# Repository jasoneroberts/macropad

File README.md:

# Macropad with a screen

A wireless macropad with MX keys, an EC11 knob and a small LCD that shows what each key does. It is built on the same nRF52840 / Zephyr / nRF Connect SDK stack as the [trackball](https://github.com/jasoneroberts/NordicMouseProject), with a 3D-printed case and a hand-soldered PCB. Started 2026-10-20.

Status 2026-10-21: concept B (12 keys, 2.0″ screen) and the SuperMini nRF52840 controller are chosen. The case model, firmware and PCB inputs exist for all three concepts; the firmware compiles but has not run on hardware yet, and nothing has been printed. Next: buy the screen and an EC11 knob and try the firmware on the nRF52840 DK.

Status 2026-11-11: the concept B main PCB is designed in full (schematic, placement, routing, ground pours) with its parts in a shared JR component library, ready to import into Altium 19 and order from JLCPCB: see `pcb/B/altium/README.md`. The controller pin map changed with it (LCD on footprint pins 5-10, rows 0/1 on P1.15/P0.02); the firmware and case follow.

| | A · Pocket | B · Studio (chosen) | C · Deck |
|---|---|---|---|
| Keys | 3 × 3 MX hot-swap | 4 × 3 MX hot-swap | 4 × 4 MX hot-swap |
| Knob (EC11) | Ø26 | Ø28 | Ø36 |
| Screen | 1.69″ ST7789V2 240 × 280, portrait | 2.0″ ST7789 320 × 240, landscape | 1.28″ GC9A01 240 × 240, round |
| Footprint on desk | 76 × 122 mm | 101 × 118 mm | 92 × 142 mm |
| Height front / rear | 12.5 / 25.1 mm | 12.5 / 24.6 mm | 12.5 / 29.5 mm |
| Tilt | 6° | 6° | 7° |
| LiPo | 603040 | 603040 | 803040 |

Heights are without the 10 mm rubber feet (add about 2 mm).

## Folder

| Path | What |
|---|---|
| `scad/macropad.scad` | The parametric model. Every dimension is a named parameter at the top. |
| `stl/<A,B,C>/print/` | `top`, `bottom`, `knob`, `clamp`, already oriented for the printer bed. |
| `stl/<A,B,C>/view/` | Every part and dummy component (PCB, switches, display, controller, battery) in the assembled position. Made by `tools/build.py`; not kept in git. |
| `stl/test_coupon.stl` | Print this first: switch holes 13.9 / 14.0 / 14.1 / 14.2 (1 to 4 dots) and two insert holes. |
| `dxf/pcb_outline_<c>.dxf` | Main PCB outline with MX centre holes (Ø4) and pillar holes (Ø2.2), for Altium. Plate-frame mm, origin at the case's front-left corner. |
| `build/report_<c>.json` | Dimensions and positions of everything, plus the fit-check result. |
| `build/viewer_<c>.glb` | Coloured assembly. Opens in Windows 3D Viewer. |
| `build/fitcheck.txt` | Overlap check between all parts. Should say `OK` for each concept. |
| `page/index.html` | The concept comparison page with 3D viewers. Made by `tools/make_page.py`; not kept in git. |
| `tools/` | `build.py` (STLs, DXF, report, fit check, GLB), `drawings.py` (plan and section SVGs), `make_page.py` + `page_template.html`, `build_firmware.sh` (Linux: installs NCS v3.3.0 and builds all six firmware variants; CI runs it too). |
| `firmware/` | Zephyr / NCS v3.3.0 app: keys, knob, LVGL screen, USB + Bluetooth HID. See `firmware/README.md`. |
| `firmware/prebuilt/` | Ready-to-flash concept B images: `macropad_B_promicro.uf2` and `macropad_B_dk.hex`. GitHub Actions also builds them on every firmware change (the run's "Artifacts"). |
| `pcb/` | The concept B board for Altium (`pcb/B/altium/`), its KiCad working copy and scripts (`pcb/B/kicad/`, `pcb/board/`), the shared JR component library (`pcb/library/`), and `generate.py`'s starting kits for all three concepts. See `pcb/README.md`. |
| `SHOPPING.md` | What to buy for B (UK prices) and what to measure when it arrives. |
| `LICENSES/` | Upstream licences for the files based on Nordic and Zephyr samples (see "Licences" below). |

## Rebuild after changing a parameter

Needs OpenSCAD 2021.01 or newer, Python 3 and `pip install trimesh manifold3d numpy scipy networkx`.

From the repo root:

```
python tools/build.py          # all concepts (or: build.py B)
python tools/drawings.py
python pcb/generate.py         # needs pip install shapely
python tools/make_page.py page
```

To export one part by hand: `openscad -D 'concept="B"' -D 'part="top_print"' -o top.stl scad/macropad.scad`. Open the file in the OpenSCAD GUI to use the Customizer for `concept` and `part`.

## Measure before printing

These come from listings or datasheets, not from parts on the bench:

- Display glass outline, thickness and where the active area sits on the glass (`LCD169`, `LCD200`, `GC9A01` tables). Board sizes and active areas are from Waveshare; glass outlines are estimates.
- EC11 body height above the PCB (`enc_body_h`, 6.5) and shaft length (`enc_shaft_l`, 15).
- Heat-set insert hole (`insert_d` 4.0, `insert_len` 4.0 for M3 × 4 short inserts).
- LiPo size (`LIPO_603040`, `LIPO_803040`).
- Switch hole (`sw_hole` 14.0): use the test coupon.

## How it's built

- Top shell = switch plate. 3 mm skin: 1.5 mm lip with the 14 mm hole, 15 mm pocket below for the MX clips. PCB top 5.0 mm below the plate top (MX standard), Kailh sockets under the PCB.
- The top surface is tilted, the bottom plate is flat, so the inside gets deeper toward the back. LiPo, controller and display stack live under the rear band.
- Display: window = active area + 0.4 mm with a 45° chamfer through a 1 mm bezel; glass in a pocket; printed clamp with two M2 screws holds the module board. Main PCB has a cut-out there; 8 wires to the module.
- Controller: SuperMini nRF52840 (chosen 2026-10-21; a nice!nano v2 also fits) on 2.5 mm headers under the PCB, component side down, USB-C (mid-mount, centred on the 1.6 mm module board) through a 13 × 7.5 mm rear opening.
- Four M3 countersunk screws into M3 heat-set inserts in the corner bosses; M2 self-tapping screws for the PCB pillars and the display clamp; slide switch slot in the right wall for the OS102011MA1QN1's actuator.
- Prints without supports: top shell face down, bottom plate and clamp flat, knob top face down. Largest part is C's top shell, 92 × 140 mm.

## Licences

No licence has been chosen for the project as a whole yet, so the default applies (all rights reserved). Two kinds of file keep their upstream licence, named by the `SPDX-License-Identifier` line at the top of the file:

- `firmware/src/BT.c` is based on Nordic's `peripheral_hids_keyboard` sample: `LicenseRef-Nordic-5-Clause` (`LICENSES/LicenseRef-Nordic-5-Clause.txt`), which allows use only with Nordic chips.
- `firmware/CMakeLists.txt` and `firmware/Kconfig` come from Zephyr's USB samples: Apache-2.0 (`LICENSES/Apache-2.0.txt`).

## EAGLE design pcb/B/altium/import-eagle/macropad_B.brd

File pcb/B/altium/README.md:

# Macropad concept B main board: Altium package

This folder takes the concept B main board into Altium Designer 19 as a **finished design**: schematic drawn, every part placed, every track routed, ground poured on both sides. You import it once with Altium's Import Wizard, check it, set the rules, repour, run the design rule check and make the Gerbers for JLCPCB.

Rough time: 30 minutes for the library and the import, 20 minutes for checks and rules, 10 minutes for Gerbers.

| | |
|---|---|
| Board | 95.3 x 110.45 mm, 2 layers, 1.6 mm, hand-soldered (0805, SOD-123, through-hole and the SuperMini on headers) |
| Parts | 40: U1 SuperMini nRF52840, 12 hot-swap sockets, 13 diodes, ENC1 encoder, power switch, reset switch, JST battery header, LCD wire pads, 3 capacitors, 2 test pads, 4 mounting holes |
| Nets | 35 |
| Copper | 253 track segments, 9 vias, a GND pour on each side. Every connection, ground included, is a track; the pours add shielding on top. KiCad's checks: 0 unrouted connections, 0 copper rule errors |
| Coordinates | mm in the case's plate frame: origin at the case's front-left corner, x to the right, y toward the screen end. The board's own bottom-left corner is at (2.85, 2.85) |

## What's in this folder

| Folder / file | What it is |
|---|---|
| `import-eagle/macropad_B.sch`, `macropad_B.brd` | **The design**, as EAGLE files for Altium 19's Import Wizard (Step 2). |
| `library/JR.lbr` | The whole JR component library (22 parts, the macropad's and the trackball carrier's) for Step 1. The same file is in `pcb/library/` in the repo. |
| `library/JR_parts.csv` | The library's part list: symbol, footprint, value, description, manufacturer, part number, LCSC number. |
| `library/JR_preview.pdf` | One page per library part: symbol, footprint and parameters. |
| `reference/macropad_B-schematic.pdf` | The schematic (A3), to read alongside the imported one. |
| `reference/macropad_B-board.pdf` | The board from the top: red = top copper, blue = bottom copper, shaded = pours. |
| `reference/placement.csv` | Every part's side, X, Y, rotation and pin 1 position. |
| `reference/connections.csv` | Every pin and the net it's on. |
| `reference/BOM.csv`, `reference/order-list.csv` | Parts list, and what to buy where, with LCSC numbers. |
| `reference/gerbers-reference/` | Gerbers and drill files made by KiCad from the same board. Compare Altium's against these (Step 6). |

## How this design was made, and why it reaches Altium as EAGLE files

The design lives in the repo as Python (`pcb/board/`): `design_b.py` holds the parts, the nets, the pin map and where each part must sit for the case; `build_board.py` places the parts and draws the outline from the case model; `route.py` routes it with Freerouting and pours the ground; `schematic.py` draws the schematic. KiCad 7 is the engine underneath: it holds the board while it's built and runs the design rule check.

Altium 19 has no KiCad importer (it arrived in Altium 20.1), but it does import EAGLE. EAGLE files are plain XML, so `export_altium.py` writes the board and the schematic in EAGLE's format, and two checks run on them before they reach you:

- `check_eagle.py` reads the two files the way Altium will: every schematic pin sits on the end of a wire of its own net, nothing touches a pin of another net, and the nets built from the schematic are exactly the board's nets (35 nets, 104 pins; the only unconnected pins are U1's spare P0.08 and the power switch's unused third pin).
- KiCad's own EAGLE importer reads the board back: all 172 pads, 253 tracks and 9 vias land within 0.003 mm of the original, on the right nets.

EAGLE has a few rules that shape what you'll see after the import. None of them change the circuit:

- **Surface-mount pads have to be on the top of an EAGLE footprint.** Parts that sit on the bottom of this board are stored the normal way and placed *mirrored* (EAGLE rotation `MR...`). Altium turns that into a part on the Bottom Layer. The hot-swap socket footprint is drawn from the socket's side for the same reason; see "Library notes" below.
- **Pin names must be unique.** The SuperMini's three GND pins arrive as `GND`, `GND@4` and `GND@23`. Pin numbers (Altium's pin *designators*) are unaffected.
- **Through-hole pads can only be round or square.** Oval pads arrive round at their narrow width: the slide switch's pins (1.5 mm) and mounting legs (2.2 mm), and the battery header's pins (1.2 mm). They're still big enough to solder; Step 4.7 says how to make them oval again.
- **There are no slots.** The encoder's two mounting-lug slots arrive as round 1.5 mm holes, with the slot's outline drawn on a mechanical layer. Step 4.6 turns them back into 2.8 x 1.5 mm slots. This one matters: the lugs won't fit a round hole.

## Before you start

1. **Unzip or copy the package** to a short path, for example `C:\Users\jason\OneDrive\Documents\Projects\WirelessTrackballProject\PCB\macropad-altium\`.
2. **Close the Gameball carrier project** in Altium if it's open, so nothing from it gets mixed in.
3. **Units:** press `Q` in any PCB view until the status bar shows mm.

## Step 1: Install the JR library (once, for every design)

The JR library is your own component library: one symbol per kind of part (a resistor, a diode, the SuperMini), one footprint per package, and one *component* per orderable part that ties a symbol to a footprint and carries the part data (value, description, manufacturer, part number, LCSC number). The macropad and the carrier both use it, and new designs can too. It lives in `D:\Jase\Nas\Engineering\PCB Design\Altium\Libraries\`.

In Altium terms you end up with:

- `JR.SchLib` (schematic symbols) and `JR.PcbLib` (footprints): the source files you edit.
- `JR.LibPkg`: an *integrated library package*, a small project that lists those two files.
- `JR.IntLib`: the compiled, read-only library that designs place parts from. You recompile it after every edit.

The same files, with the Gameball relink table and a parts preview, are in `D:\Jase\Nas\Engineering\PCB Design\Altium\Libraries\`; use that copy for every board. Once `JR.IntLib` exists, install it for all projects: Components panel menu » **File-based Libraries Preferences » Installed » Install**.

Steps:

1. **File » Import Wizard » Next**, pick **EAGLE Projects and Designs**, **Next**.
2. **Design files:** add nothing. **Next.**
3. **Library files:** **Add** `library\JR.lbr`. **Next.**
4. **Settings page:** tick **Log All Errors / Warnings / Events**. Set the **output directory** to `D:\Jase\Nas\Engineering\PCB Design\Altium\Libraries\`. **Next**, then **Finish**.
5. You now have `JR.SchLib` and `JR.PcbLib` in that folder (open them from **File » Open** if the wizard didn't). Open the SchLib, pick a few components in the **SCH Library** panel, and check:
   - the **Parameters** list has `MANUFACTURER`, `MPN`, `LCSC` and `DESCRIPTION` (and the **Comment** shows the value, for example `1N4148W`);
   - the **Models** list has a footprint with the same name as in `JR_parts.csv`, and its preview shows the footprint.
6. **Make the package:** **File » New » Project**, type **Integrated Library**, name `JR`, location `D:\Jase\Nas\Engineering\PCB Design\Altium\Libraries\`. Right-click `JR.LibPkg` in the **Projects** panel » **Add Existing to Project** » pick `JR.SchLib` and `JR.PcbLib`. **File » Save All.**
7. **Compile it:** right-click `JR.LibPkg` » **Compile Integrated Library JR.LibPkg**. The Messages panel should show no errors. Altium writes `Project Outputs for JR\JR.IntLib` and adds it to the **Components** panel. If the panel doesn't list it: **Components panel » ☰ » File-based Libraries Preferences » Installed » Install** and pick the `.IntLib`.
8. **Optional tidy-up**, which you can do any time (recompile afterwards):
   - Rename the parameters to Altium's usual names with **Tools » Parameter Manager** in the SchLib: `MANUFACTURER` → `Manufacturer`, `MPN` → `Manufacturer Part Number`, `DESCRIPTION` → the component's **Description** field.
   - Give the SuperMini's GND pins plain names (`GND@4` → `GND`).

*Why an IntLib and not just the two files?* The compiled library carries the symbol, footprint and parameters together, and Altium checks on compile that every symbol pin has a pad to go to. Designs then link to `JR.IntLib`, so a change you make once (a footprint fix, a new LCSC number) reaches every design with **Tools » Update From Libraries**.

## Step 2: Import the design

1. **File » Import Wizard » Next**, pick **EAGLE Projects and Designs**, **Next**.
2. **Design files:** **Add** `import-eagle\macropad_B.sch` and `import-eagle\macropad_B.brd` (Ctrl-click both, or one after the other). **Next.**
3. **Library files:** add nothing (the design files carry their own copy of the parts). **Next.**
4. **Layer mapping** (if your version shows the grid; otherwise Altium uses its defaults and you check the result in Step 3):

   | EAGLE layer | Altium layer | What's on it |
   |---|---|---|
   | 1 Top / 16 Bottom | Top Layer / Bottom Layer | Tracks, pads, the two GND pours |
   | 20 Dimension | Mechanical 1 | **Board outline** |
   | 21 tPlace / 22 bPlace | Top Overlay / Bottom Overlay | Silkscreen |
   | 25 tNames / 26 bNames | Top Overlay / Bottom Overlay | Designators |
   | 27 tValues / 28 bValues | Top Overlay / Bottom Overlay | Values (hidden) |
   | 41 tRestrict / 42 bRestrict | Keep-Out (top / bottom copper) | No copper round the four M2 screw holes |
   | 46 Milling | a spare mechanical layer, for example Mechanical 4 | Outline of the encoder's two lug slots |
   | 51 tDocu / 52 bDocu | Mechanical 13 / Mechanical 14 | Part bodies (assembly drawing) |

5. **Settings page:**
   - **General:** tick **Log All Errors / Warnings / Events**.
   - **Schematic:** **untick Recognize powerports and Recognize ports.** This design connects everything by wires and net labels; with these ticked, Altium can turn parts whose names match its patterns into port symbols.
   - **PCB:** leave **Generate 3D body** unticked.
   - **Output directory:** a new empty folder, for example `...\macropad-altium\altium-project\`.
6. **Next**, wait, **Finish**. Read the log: font and unused-layer warnings are fine; tell me about anything else.
7. **One project:** if the Projects panel shows two projects (one with the `.SchDoc`, one with the `.PcbDoc`), right-click the one with the `.SchDoc` » **Add Existing to Project** » pick the `.PcbDoc`, then close the other project. **File » Save All.**
8. **Link schematic and PCB parts:** EAGLE files don't carry Altium's hidden Unique IDs, so link them once by designator. Open the `.PcbDoc`, **Project » Component Links**, **Add Pairs Matched By** with *Designator* ticked, check all 40 parts are in the matched list, **Perform Update**. **File » Save All.**

## Step 3: Check the import (10 minutes)

1. **Compile:** **Project » Compile PCB Project**. Open **Messages**. No errors expected. EAGLE has no no-connect markers, so U1 pin 2 (P0.08) and SW_PWR pin 3 may be listed as unconnected: that's correct. Put **Place » Directives » Generic No ERC** on them for a clean list.
2. **Schematic and PCB agree:** in the `.PcbDoc`, **Design » Update PCB Document**. After Step 2.8 the list should be empty, or only offer *Rooms* and *Component Classes* (untick those). If it wants to change nets or replace parts, click **Cancel** and tell me what it lists.
3. **Board shape:** press `2`. The board is the L shape: full width at the front (keys), only the right-hand strip at the back (controller and knob), with the big opening for the screen at the back left and a dip round the screen clamp's pillar. Three corner notches (front left, front right, back right) clear the case's screw bosses; the fourth boss sits in the screen opening, off the board. If the board area is a plain rectangle: click the outline on Mechanical 1, press `Tab` to select all of it, **Design » Board Shape » Define from selected objects**.
4. **Origin:** the EAGLE coordinates are the case's plate frame, so Altium's origin should already be the case's front-left corner, 2.85 mm below and left of the board's corner. If the numbers below don't match, **Edit » Origin » Set** and type or click (0, 0) accordingly.
5. **Spot-check five parts.** Click the part, read X, Y and Layer in **Properties**; then click its pin 1 pad and check the pad's position. Pin 1 is the unambiguous check for bottom-side parts, because Altium and EAGLE count rotation differently for mirrored parts.

   | Part | Layer | X | Y | Pin 1 at |
   |---|---|---|---|---|
   | U1 | Bottom | 82.000 | 96.250 | (89.620, 110.220), square pad, back right |
   | ENC1 | Top | 82.000 | 87.650 | pin A (79.500, 80.150), square pad |
   | SW1 | Bottom | 21.925 | 55.625 | pad 1 (14.840, 58.165) |
   | J2 | Bottom | 93.600 | 105.140 | pin 1 (93.600, 105.140), square pad, back end |
   | SW_RST | Bottom | 74.500 | 66.125 | pad 1 (71.500, 64.250) |

   `reference/placement.csv` has the rest.
6. **Nets:** **PCB panel » Nets**: 35 nets. 3V3_SW, COL0-COL4, DBG_TX, ENC_A, ENC_B, GND, K1-K12, K_PUSH, LCD_BL, LCD_CS, LCD_DC, LCD_MOSI, LCD_RST, LCD_SCK, NRST, ROW0-ROW2, VBAT, VBAT_SW. `reference/connections.csv` lists every pin.
7. **Tracks:** compare with `reference/macropad_B-board.pdf`. Nearly all routing is on the bottom, so the top stays one solid ground plane under the keys.

## Step 4: Rules, pours and the two fix-ups

Open **Design » Rules**. These are the values the board was routed and checked with in KiCad, with margin over JLCPCB's standard limits.

1. **Net class:** **Design » Classes » Net Classes** should have `power` with GND, VBAT, VBAT_SW and 3V3_SW. Add it if the import didn't.
2. **Electrical » Clearance:** 0.2 mm. Add a second Clearance rule, scope *InPolygon* to *All*, 0.3 mm, priority above the first: the pours keep 0.3 mm from everything else, as they did in KiCad.
3. **Routing » Width:** default min 0.2, preferred 0.25, max 1.0 mm. Second rule, scope *InNetClass('power')*: min 0.3, preferred 0.4, max 1.0 mm, priority above the default.
4. **Routing » Routing Via Style:** diameter 0.6 mm, hole 0.3 mm.
5. **Manufacturing:** **Hole Size** min 0.3, max 4.1 mm (the MX switch centre holes are 4.0 mm). **Board Outline Clearance** 0.3 mm. **Hole To Hole Clearance** 0.25 mm. **Minimum Annular Ring** 0.15 mm.
6. **Encoder lug slots.** Do this in the library so every design gets it: open `JR.PcbLib`, footprint `RotaryEncoder_EC11_Switch_NPTH`. Double-click each of the two unnamed holes at (0, ±5.6): **Hole Type: Slot**, **Hole Size 1.5 mm**, **Length 2.8 mm**, **Rotation 0**, **Plated: off**. Pad size equal to the hole, no copper. Save, recompile `JR.LibPkg`. In the design, in the `.PcbDoc`: **Tools » Update From PCB Libraries**, pick ENC1 only. On the board the slots then run front to back at x = 76.4 and 87.6, between U1's two pin rows, 0.42 mm from U1's pads. Delete the slot outlines on the milling layer afterwards (they were only there to show where the slots go).
7. **Oval pads (optional):** in the PcbLib, `SW_Slide_SPDT_Angled_CK_OS102011MA1Q` pins 1-3 back to 1.5 x 2.5 mm *Round* (Altium draws that as an oval) and MP1/MP2 to 2.2 x 3.5 mm; `JST_PH_S2B-PH-K_1x02_P2.00mm_Horizontal` pins to 1.2 x 1.75 mm. Update the design from the library as in item 6.
8. **Pours:** the two GND polygons (top and bottom) came in with the design, already shaped: inset 0.3 mm from the edge, and with a gap over the whole SuperMini so no copper sits near its antenna. Check each one's net is `GND`, **Pour Over All Same Net Objects**, **Remove Dead Copper** ticked. Then **Tools » Polygon Pours » Repour All**.
9. **Pour connections:** **Plane » Polygon Connect Style:** *Relief Connect*, 4 entries, conductor width 0.4 mm, air gap 0.3 mm. That's what KiCad used. Repour again if you changed it.
10. **Screw-hole keep-outs:** the four M2 holes (H1-H4) each have a round keep-out on both copper layers, 2.6 mm radius, so the screw heads underneath can't touch copper. Check they came through (they show on the Keep-Out layer). If not, draw a 5.2 mm keep-out circle round each hole on Top and Bottom.

## Step 5: Design rule check

**Tools » Design Rule Check » Run Design Rule Check.** Expected:

- **0 Un-Routed Net Constraint** violations. All 12 ground pads have ground tracks, so this holds even before the pours are filled; if Altium reports a pour as unconnected *dead copper*, the Remove Dead Copper option in Step 4.8 takes it out.
- **0 clearance, width, short-circuit or hole-size violations.**
- **Silkscreen warnings are fine:** some stock footprints draw silk across their pads (the hot-swap socket and the slide switch, for example), and the SuperMini's outline runs off the board at the back-right notch. JLCPCB clips silk off pads and the board edge. Fix them if you like the board tidy.

## Step 6: Gerbers and drill files for JLCPCB

1. **Gerbers:** **File » Fabrication Outputs » Gerber Files**. Units *Millimeters*, format *4:4* (or *Inches 2:4*, both fine for JLC). **Layers** tab: **Plot Layers » Used On**; among the mechanical layers tick **only Mechanical 1** (the outline). **OK**.
2. **Drill:** **File » Fabrication Outputs » NC Drill Files**, same units and format. Tick **Generate separate NC Drill files for plated & non-plated holes**. **OK**, and **OK** on the drill-size pop-up.
3. **Compare with the reference:** open both sets in a Gerber viewer (JLCPCB's upload preview, or Altium's **File » Open** on the `.GTL` etc., which opens CAMtastic). Things to see in Altium's set: the L-shaped outline with three boss notches and the shallow dip in the back edge; the encoder's two **slots** (not round holes) in the non-plated drill file; 9 vias; no copper under the SuperMini; the GND pour on both sides.
4. **Zip** the Gerber and drill files from `Project Outputs for ...`.
5. **Order at JLCPCB:** 2 layers, 1.6 mm, 5 boards, any colour, HASL with lead (easiest to hand-solder). The board is over 100 mm in one direction, so it costs a few pounds more than the 100 x 100 mm price.

`reference/gerbers-reference/` is a complete set from KiCad (plate-frame coordinates, slots in the NPTH drill file). If Altium's output ever disagrees with it, ask me before ordering.

## Step 7: Check before ordering boards

A mistake in any of these means a new board. Print the board 1:1 first (**File » Page Setup**, *Scaled Print*, scale 1.00; check the board measures 95.3 mm across) and lay real parts on the paper.

1. **SuperMini at the back right, under the board.** U1 hangs under the board on its headers with its components facing down toward the desk (its plain back toward the PCB), USB-C toward the back wall. Turn the print over and lay a SuperMini on the bottom view, components up: its pin labels must match the schematic (pin 1 = P0.06 at the back right seen from the top, B+ at the back left), and USB must point at the back edge. The pin positions are the standard Pro Micro ones (rows 15.24 mm apart, 2.54 mm pitch).
2. **Encoder.** Fit a real PEC11R-4220F-S0024 through the print: 5 pins (A, C, B on one side; S1, S2 on the other) and the two lugs on the slots. The lugs and pins are trimmed flush on the bottom before U1 goes on, because U1 sits right under them.
3. **Power switch reach.** The OS102011MA1QN1's actuator should stick 0.9 mm out of the right-hand wall at y = 72. The case slot has been adjusted to the switch's 2 x 4 mm actuator; print the case's right wall section if you want to try it before the PCB arrives.
4. **Battery polarity.** J1 pin 1 (square pad, the one nearer the front) is `VBAT` (+), pin 2 is GND; the plug goes in from the left. LiPo leads come both ways round: check yours before plugging in, and swap the pins in the plug if it's reversed.
5. **LCD cable order.** J2 pins 1-8 are VCC, GND, DIN, CLK, CS, DC, RST, BL from the back, which is the Waveshare cable order. Check the colours on your cable against the module's labels when it arrives.
6. **Heights.** U1 on 2.5 mm low-profile headers; nothing on the top side may poke up more than 2 mm (the gap under the case skin), so trim every through-hole joint flush on the top.

## Assembly order

1. Diodes D1-D13 and capacitors C1-C3 (bottom).
2. Hot-swap sockets SW1-SW12 (bottom).
3. SW_RST, SW_PWR, J1 (bottom).
4. ENC1 from the top; **trim its five pins and two lugs flush underneath**, and put Kapton tape over the area.
5. U1 on its low-profile headers (bottom). Trim the pins flush on the top.
6. LCD cable into J2 from the bottom, solder on the top, trim flush.

## Library notes

- **The hot-swap socket footprint is drawn from the socket's side.** EAGLE (and so the import) only allows surface-mount pads on top, so `SW_Kailh_MX_Hotswap` has its pads on the top layer and is mirrored left-to-right. Placed on the **bottom** layer it comes out right: the holes line up with the switch above, the pads land on the bottom copper where the socket is soldered. Always place it on the bottom. If you'd rather have it the Altium way (drawn from the top, pads on the bottom layer), redraw it in the PcbLib.
- The JR library also holds the carrier's parts (XIAO nRF52840, SS14, DMG2305UX, 0805 resistors and capacitors, the connectors). The carrier project stays linked to its own imported library until you decide to switch it over.
- To add a part later: draw the symbol in `JR.SchLib` (or reuse one: every resistor uses `R`), the footprint in `JR.PcbLib`, set the parameters (`Manufacturer`, `Manufacturer Part Number`, `LCSC`, `Description`), recompile. `JR_parts.csv` shows the pattern.

## What changed elsewhere with this board

- **Controller pin map:** footprint pins 5-10 now carry the LCD's six signals in the Waveshare cable order (P0.17 MOSI, P0.20 SCK, P0.22 CS, P0.24 DC, P1.00 RST, P0.11 backlight), so they run straight across to J2. Rows 0 and 1 moved to P1.15 and P0.02. The firmware's board overlay, `pcb/generate.py` and `pcb/README.md` are updated to match, and the firmware rebuilt.
- **Case:** knob moved 1 mm left to x = 82 (centred over the SuperMini, so the encoder's lug slots fall between its pin rows); the PCB outline opens the screen cut-out to the back and left edges and clears the screen clamp pillar by 0.5 mm; boss notches 8.8 mm across; the case trims 0.4 mm round the PCB edge at board height; USB-C opening raised for the SuperMini's mid-mount connector; power switch modelled as the OS102011MA1QN1.

## Rebuilding this package

Everything here is generated. After changing the design, from the repo root on a machine with KiCad 7 and Freerouting:

```
/usr/bin/python3 pcb/library/src/build_library.py            # JR library
/usr/bin/python3 pcb/board/build_board.py pcb/B/kicad        # place parts, outline, pours
/usr/bin/python3 pcb/board/route.py pcb/B/kicad freerouting-1.9.0.jar
/usr/bin/python3 pcb/board/check.py pcb/B/kicad/macropad_B.kicad_pcb
/usr/bin/python3 pcb/board/export_altium.py pcb/B/kicad pcb/B/altium
python3 pcb/board/check_eagle.py pcb/B/altium/import-eagle
```

Once you've imported into Altium and started editing there, the Altium project is the master copy and these files are history.

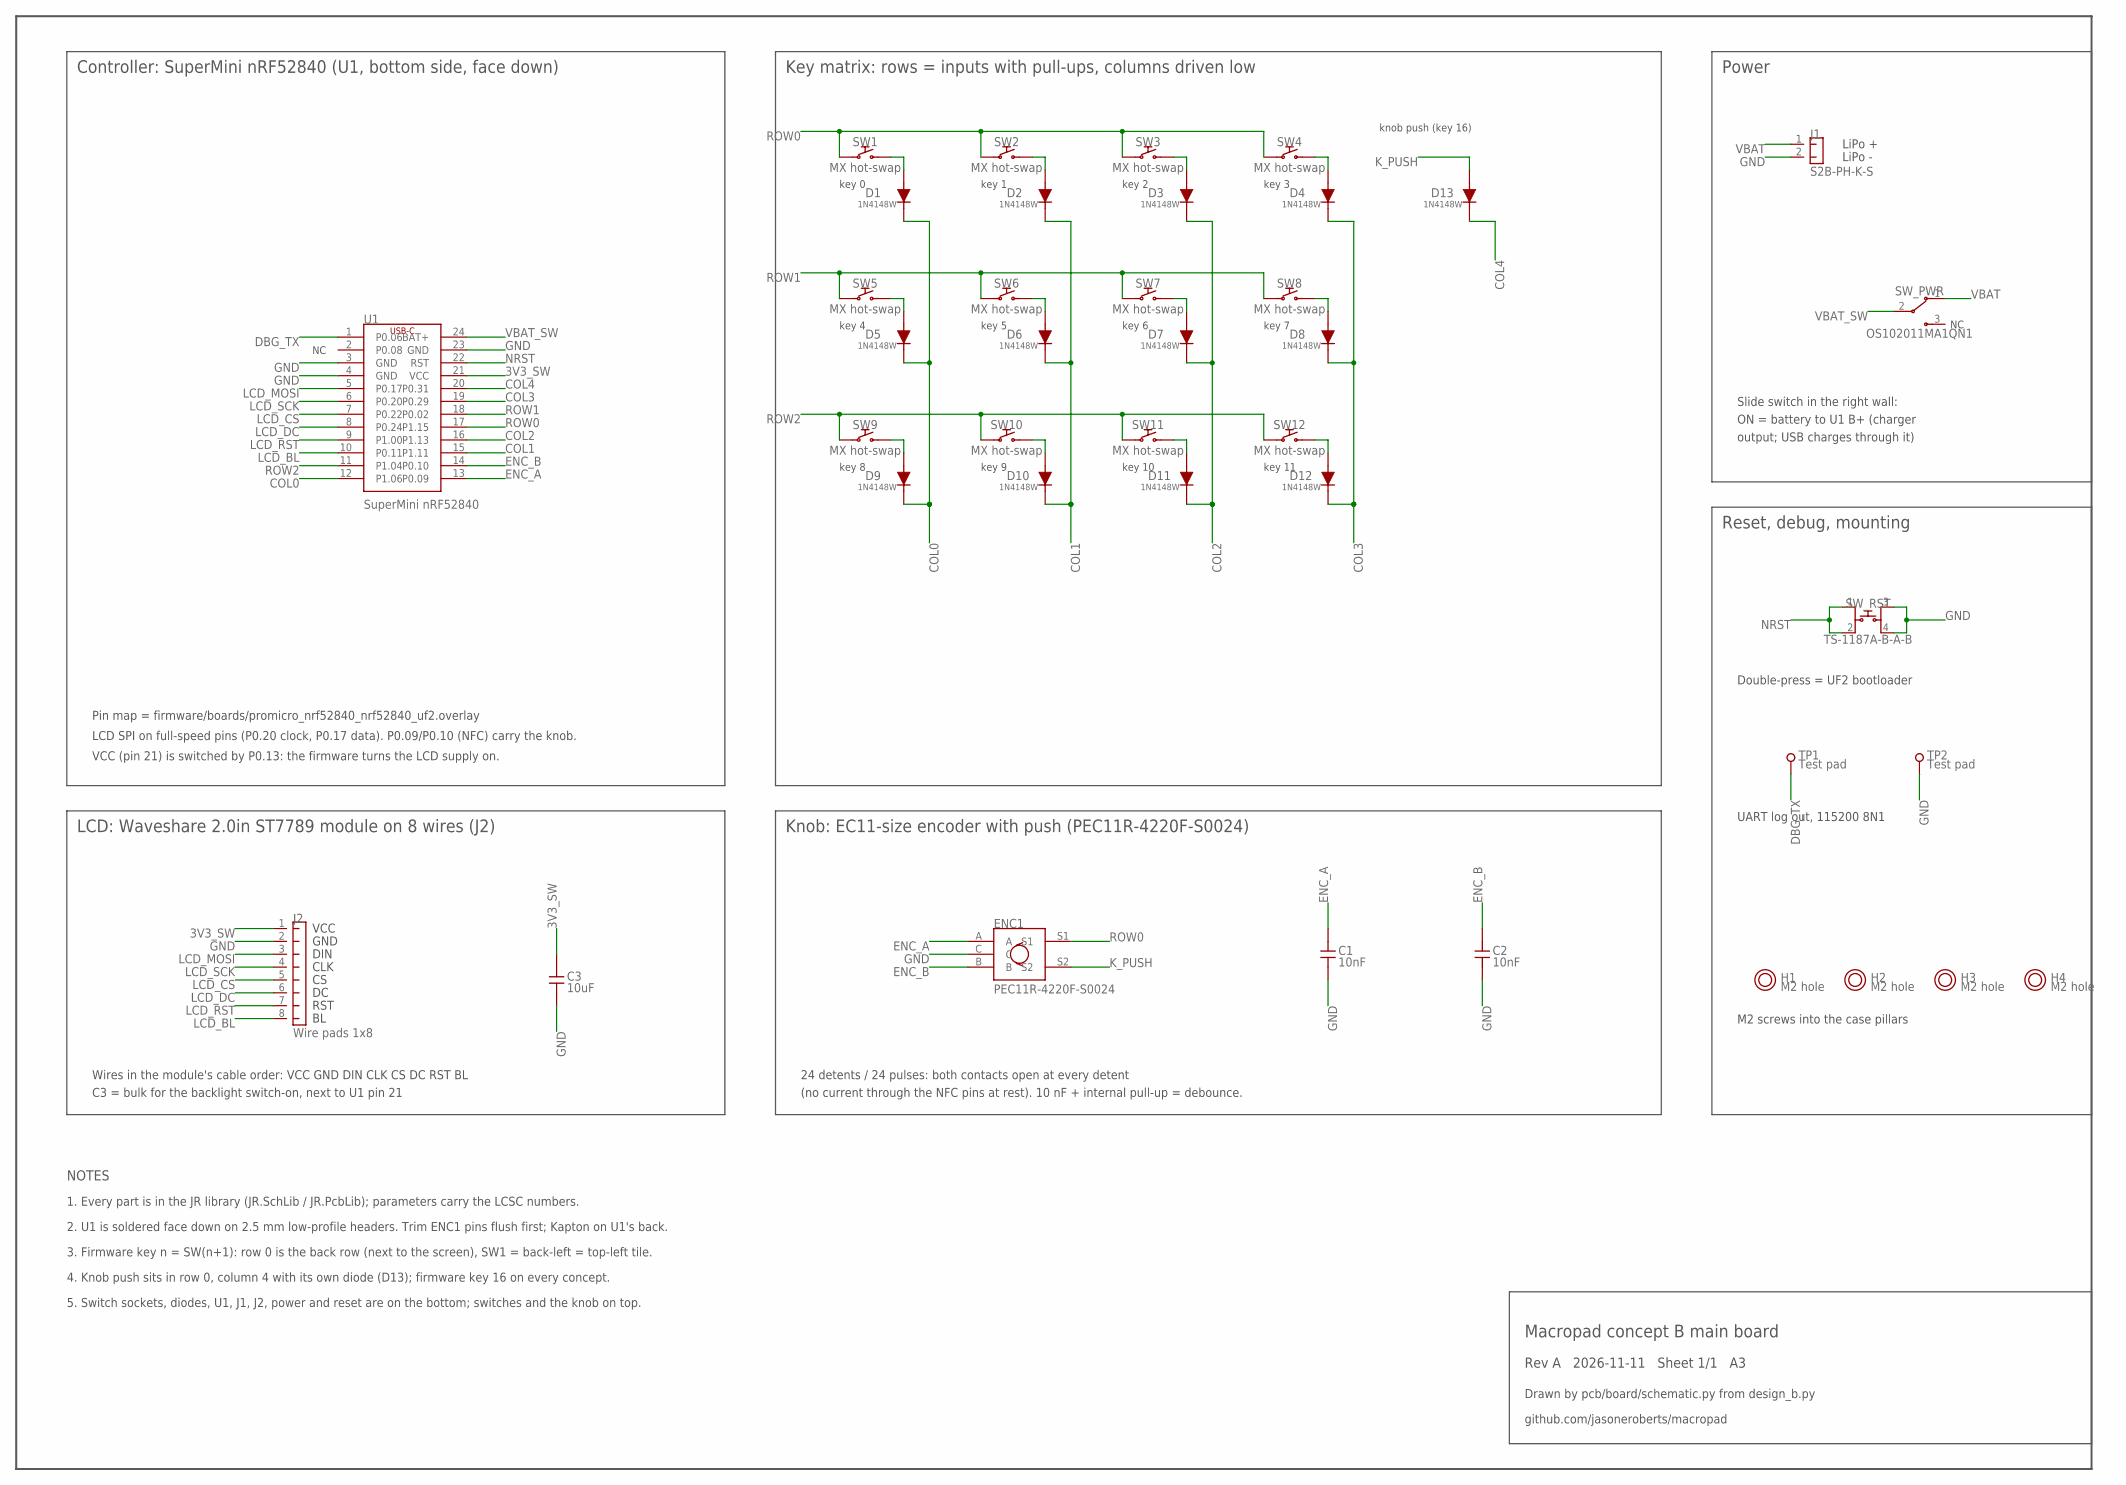
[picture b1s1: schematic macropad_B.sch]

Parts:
C1, C2: 10nF; C_0805_2012Metric; MPN CL21B103KBANNNC; LCSC C1710
C3: 10uF; C_0805_2012Metric; MPN CL21A106KAYNNNE; LCSC C15850
D1, D2, D3, D4, D5, D6, D7, D8, D9, D10, D11, D12, D13: 1N4148W; D_SOD-123; MPN 1N4148W; LCSC C81598
ENC1: PEC11R-4220F-S0024; RotaryEncoder_EC11_Switch_NPTH; MPN PEC11R-4220F-S0024; LCSC C143797
H1, H2, H3, H4: M2 hole; MountingHole_2.2mm_M2
J1: S2B-PH-K-S; JST_PH_S2B-PH-K_1x02_P2.00mm_Horizontal; MPN S2B-PH-K-S(LF)(SN); LCSC C173752
J2: Wire pads 1x8; PinHeader_1x08_P2.54mm_Vertical
SW1, SW2, SW3, SW4, SW5, SW6, SW7, SW8, SW9, SW10, SW11, SW12: MX hot-swap; SW_Kailh_MX_Hotswap; MPN CPG151101S11; LCSC C2803348
SW_PWR: OS102011MA1QN1; SW_Slide_SPDT_Angled_CK_OS102011MA1Q; MPN OS102011MA1QN1; LCSC C226259
SW_RST: TS-1187A-B-A-B; SW_Push_1P1T_XKB_TS-1187A; MPN TS-1187A-B-A-B; LCSC C318884
TP1, TP2: Test pad; TestPoint_Pad_D1.5mm
U1: SuperMini nRF52840; SuperMini_nRF52840; MPN SuperMini nRF52840

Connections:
3V3_SW: C3.1, J2.1, U1.21 (VCC)
COL0: D1.1 (K), D5.1 (K), D9.1 (K), U1.12 (P1.06)
COL1: D2.1 (K), D6.1 (K), D10.1 (K), U1.15 (P1.11)
COL2: D3.1 (K), D7.1 (K), D11.1 (K), U1.16 (P1.13)
COL3: D4.1 (K), D8.1 (K), D12.1 (K), U1.19 (P0.29)
COL4: D13.1 (K), U1.20 (P0.31)
DBG_TX: TP1.1, U1.1 (P0.06)
ENC_A: C1.1, ENC1.A, U1.13 (P0.09)
ENC_B: C2.1, ENC1.B, U1.14 (P0.10)
GND: C1.2, C2.2, C3.2, ENC1.C, J1.2, J2.2, SW_RST.3, SW_RST.4, TP2.1, U1.3 (GND), U1.4 (GND), U1.23 (GND)
K1: D1.2 (A), SW1.2
K2: D2.2 (A), SW2.2
K3: D3.2 (A), SW3.2
K4: D4.2 (A), SW4.2
K5: D5.2 (A), SW5.2
K6: D6.2 (A), SW6.2
K7: D7.2 (A), SW7.2
K8: D8.2 (A), SW8.2
K9: D9.2 (A), SW9.2
K10: D10.2 (A), SW10.2
K11: D11.2 (A), SW11.2
K12: D12.2 (A), SW12.2
K_PUSH: D13.2 (A), ENC1.S2
LCD_BL: J2.8, U1.10 (P0.11)
LCD_CS: J2.5, U1.7 (P0.22)
LCD_DC: J2.6, U1.8 (P0.24)
LCD_MOSI: J2.3, U1.5 (P0.17)
LCD_RST: J2.7, U1.9 (P1.00)
LCD_SCK: J2.4, U1.6 (P0.20)
NRST: SW_RST.1, SW_RST.2, U1.22 (RST)
ROW0: ENC1.S1, SW1.1, SW2.1, SW3.1, SW4.1, U1.17 (P1.15)
ROW1: SW5.1, SW6.1, SW7.1, SW8.1, U1.18 (P0.02)
ROW2: SW9.1, SW10.1, SW11.1, SW12.1, U1.11 (P1.04)
VBAT: J1.1, SW_PWR.1
VBAT_SW: SW_PWR.2 (COM), U1.24 (BAT+)

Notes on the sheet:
Controller: SuperMini nRF52840 (U1, bottom side, face down)
Pin map = firmware/boards/promicro_nrf52840_nrf52840_uf2.overlay
LCD SPI on full-speed pins (P0.20 clock, P0.17 data). P0.09/P0.10 (NFC) carry the knob.
VCC (pin 21) is switched by P0.13: the firmware turns the LCD supply on.
Key matrix: rows = inputs with pull-ups, columns driven low
key 0
key 1
key 2
key 3
key 4
key 5
key 6
key 7
key 8
key 9
key 10
key 11
knob push (key 16)
Knob: EC11-size encoder with push (PEC11R-4220F-S0024)
24 detents / 24 pulses: both contacts open at every detent
(no current through the NFC pins at rest). 10 nF + internal pull-up = debounce.
LCD: Waveshare 2.0in ST7789 module on 8 wires (J2)
VCC
GND
DIN
CLK
RST
Wires in the module's cable order: VCC GND DIN CLK CS DC RST BL
C3 = bulk for the backlight switch-on, next to U1 pin 21
Power
LiPo +
LiPo -
Slide switch in the right wall:
ON = battery to U1 B+ (charger
output; USB charges through it)
Reset, debug, mounting
Double-press = UF2 bootloader
UART log out, 115200 8N1
M2 screws into the case pillars
NOTES

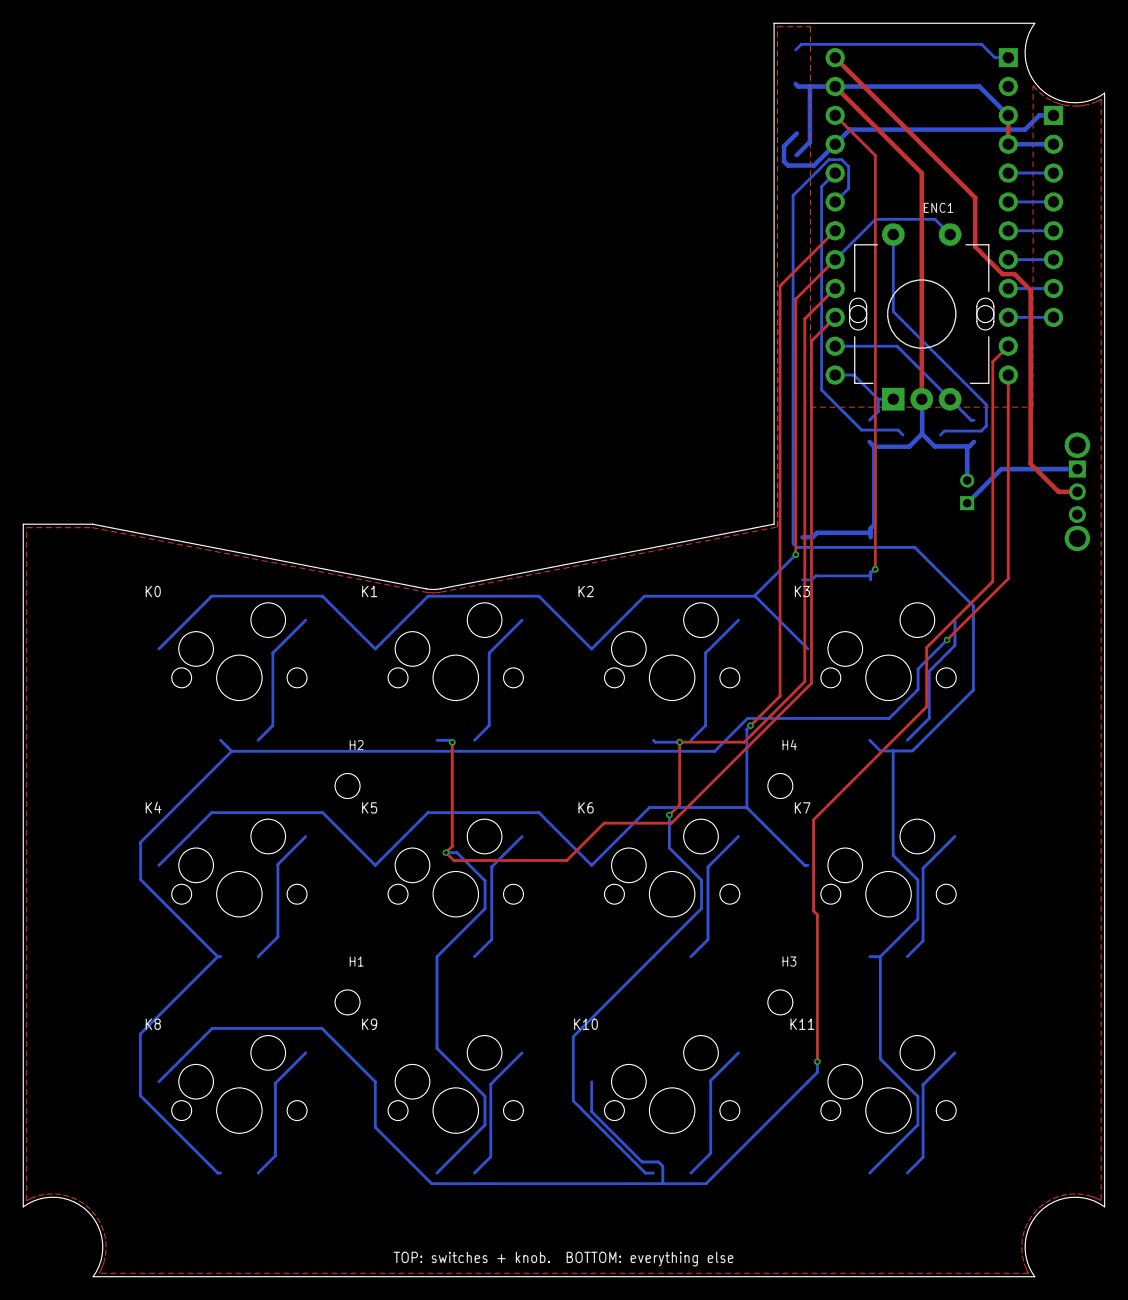
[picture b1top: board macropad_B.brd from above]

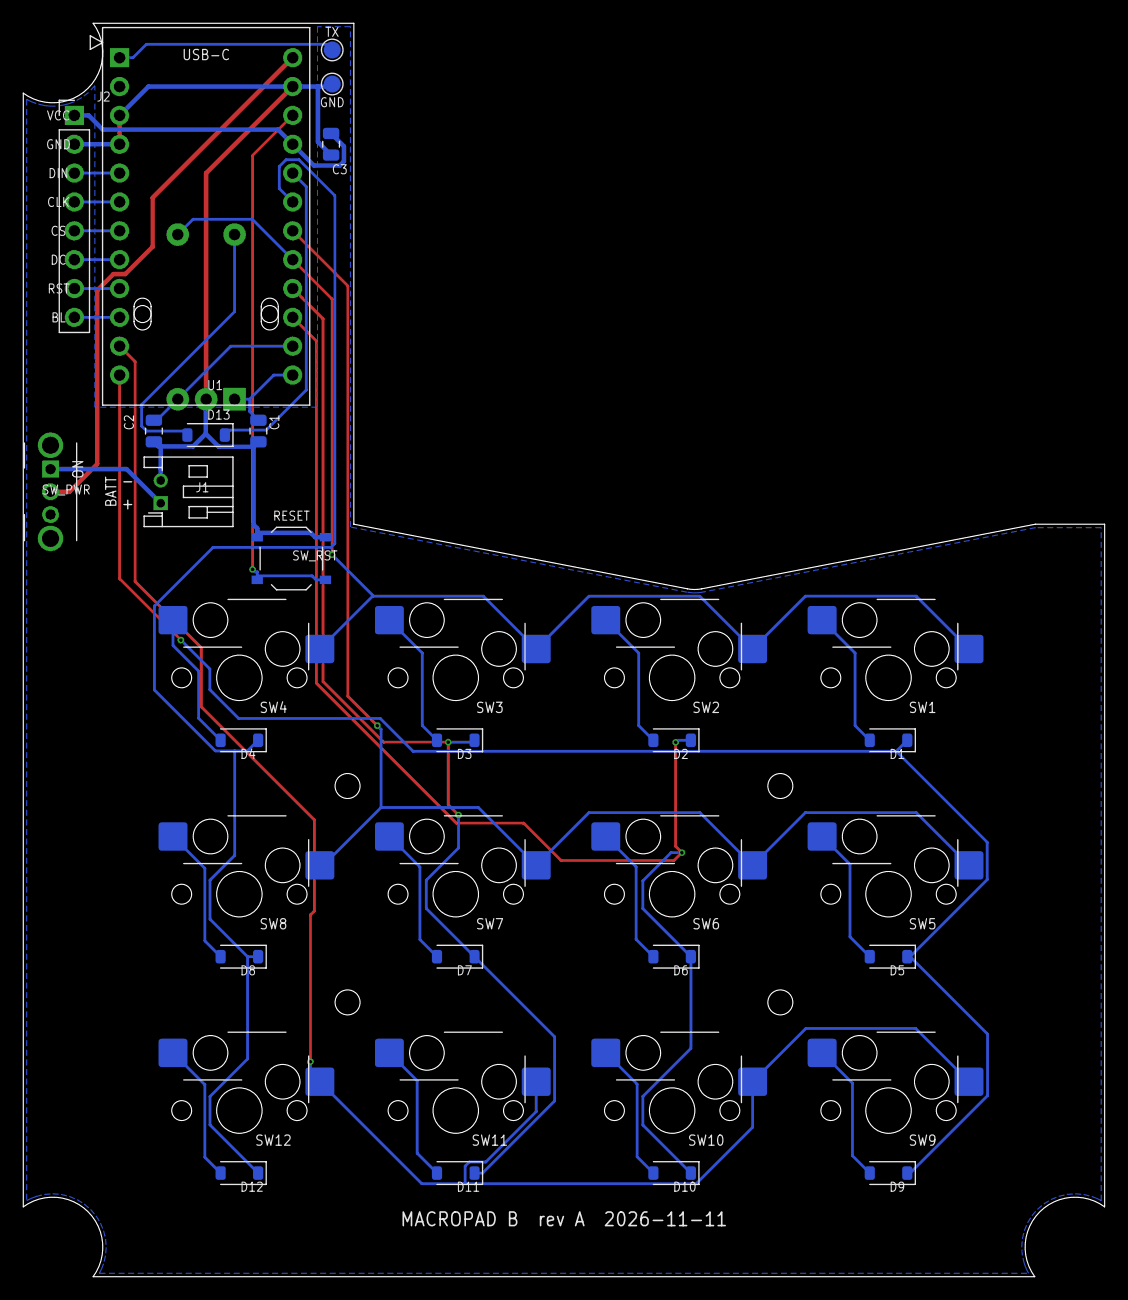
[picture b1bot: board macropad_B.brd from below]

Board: 2 copper layers, 95.2 x 110.3 mm, 40 parts (35 on the bottom side), 35 nets.

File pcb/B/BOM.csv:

Designators,Qty,Value,Manufacturer,Manufacturer part number,Package,Est. unit GBP,Description
"C1, C2",2,10nF,,,0805,0.02,Encoder debounce (with the internal pull-up)
C3,1,10uF,,,0805,0.05,LCD supply bulk (backlight switch-on)
"D1, D2, D3, D4, D5, D6, D7, D8, D9, D10, D11, D12, D13",13,1N4148W,Diodes Inc,1N4148W-7-F,SOD-123,0.03,Matrix diode
ENC1,1,EC11 encoder with switch,Alps Alpine (or generic EC11),EC11E15244G1,"EC11, THT, 15-20 mm D-shaft",1.8,"Knob: volume, push = mute"
"H1, H2, H3, H4",4,M2 hole,,,2.2 mm NPTH,,M2 self-tapping screw into the case pillar
J1,1,Battery,JST,B2B-PH-K-S(LF)(SN),"JST PH 2-pin, THT, vertical",0.2,LiPo plug. Check the cell's lead polarity before plugging in
J2,1,LCD wires,,,"8 x 1.0 mm plated holes, 2.54 mm pitch",,Solder the module's cable here (Waveshare order)
"SW1, SW2, SW3, SW4, SW5, SW6, SW7, SW8, SW9, SW10, SW11, SW12",12,MX hot-swap socket,Kailh,CPG151101S11,MX hot-swap socket (pads on bottom),0.12,"Key socket, switch plugs in from the top"
SW_PWR,1,Power switch,generic,SK12D07VG4,"SPDT slide, right-angle THT, 2.54 mm",0.3,Battery on/off. Actuator pokes out of the right wall slot. MEASURE vs case slot
SW_RST,1,Reset,C&K,PTS636 SM25 SMTR LFS,"6 x 3.5 mm tact, gull-wing",0.25,Double-press = UF2 bootloader (case open)
TP1,1,DBG_TX,,,1.5 mm test pad,,"UART log out (115200), optional"
TP2,1,GND,,,1.5 mm test pad,,"UART log out (115200), optional"
U1,1,SuperMini nRF52840,generic (or nice!nano v2),nice!nano v2 compatible,"Pro Micro 24-pin DIP, 2.54 mm, rows 15.24 mm apart",4.5,"nRF52840 module with LiPo charger and USB-C. Bottom side, components facing down, on 2.5 mm low-profile headers; no headers on the 3 inner pins (P1.01, P1.02, P1.07)"
LCD,1,Waveshare 2inch LCD Module (ST7789V 240x320),Waveshare,,module,11.0,"Screen, sits in the case window"
BT1,1,"603040 LiPo 3.7 V ~800 mAh, JST-PH lead",,,pouch cell,6.0,"Under the display band, on the bottom plate"

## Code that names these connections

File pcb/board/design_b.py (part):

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    (24, "B+", "", "VBAT_SW"),
]
# Waveshare LCD cable order (VCC, GND, DIN, CLK, CS, DC, RST, BL)
J2_PINS = [(1, "VCC", "3V3_SW"), (2, "GND", "GND"), (3, "DIN", "LCD_MOSI"), (4, "CLK", "LCD_SCK"), (5, "CS", "LCD_CS"),
           (6, "DC", "LCD_DC"), (7, "RST", "LCD_RST"), (8, "BL", "LCD_BL")]

ROWS, COLS = REPORT["rows"], REPORT["cols"]          # 3 x 4 keys; the knob push is column 4
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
